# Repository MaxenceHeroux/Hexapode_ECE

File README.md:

# Hexapode ECE

Robot hexapode (6 pattes, 18 servos Dynamixel AX-12A) du FabLab ECE MAKERS,
piloté par une Raspberry Pi 4 sous Ubuntu 22.04 / ROS 2 Humble. Ce dépôt
contient la carte électronique d'alimentation, le code de pilotage des servos,
le modèle et la marche sous ROS 2, et la documentation de mise en route.

Version actuelle : **v1.0.0** — voir [CHANGELOG.md](CHANGELOG.md).

## Ce que sait faire le robot

| | |
|---|---|
| **Marcher** | trépied avec recouvrement des appuis (aussi tétrapode, onde) piloté au clavier ou par Foxglove (`/cmd_vel`) : avancer, reculer, crabe, tourner ; jusqu'à 0,22 m/s et 0,8 rad/s |
| **Régler sa hauteur** | 50 à 150 mm en marchant (`t` / `b`), l'écart des pieds s'adapte tout seul aux butées |
| **Se stabiliser (IMU)** | tient son cap, reste horizontal si le sol penche, ne s'affaisse plus à chaque pas, s'arrête s'il bascule ; la rotation est asservie au gyroscope (compense le patinage) |
| **Faire des figures** | coucou, danse, cabrer, cœur (fenêtre « Actions hexapode ») |
| **Se dépanner** | remise en route des moteurs en une touche (`r`), servos bloqués remis en route automatiquement, reconnexion si la liaison décroche |
| **Marcher sans fil** | la Pi fait son hotspot Wi-Fi au démarrage, servos et IMU démarrent seuls ; le câble reste prioritaire quand il est branché |
| **Se voir** | modèle 3D (maillages SolidWorks) dans RViz et Foxglove |

## Démarrage rapide

Tout se lance depuis le PC (Ubuntu + ROS 2 Humble) avec **une seule commande** :

```bash
cd ~/Hexapode2026/Hexapode_ECE/ros2_ws
./hexapode.sh                   # simulation : marche + Foxglove + clavier (aucun servo ne bouge)
./hexapode.sh dry               # + pont vers le robot SANS envoi (vérifie servos et butées)
./hexapode.sh robot             # le robot se lève puis marche — PC et Pi reliés par CÂBLE
./hexapode.sh robot-distance    # pareil SANS CÂBLE : le PC rejoint le hotspot Wi-Fi de la Pi (voir hotspot.md)
./hexapode.sh dry-distance      # vérification sans câble
```

Le script règle l'environnement ROS (CycloneDDS, liaison câble ou Wi-Fi), arrête une
session oubliée, ouvre **Foxglove** (déjà connecté) et une fenêtre **« Teleop hexapode »**,
puis lance la marche et, selon le mode, le pont vers le robot. `robot-distance` allume en
au hotspot de la Pi (sauf si le câble est branché : il reste prioritaire), attend la Pi et
démarre `leg_server` dessus si besoin.

**Piloter** (clavier AZERTY, dans « Teleop hexapode ») :

| Touche | Effet |
|---|---|
| `i` / `,` | avancer / reculer (maintenir la touche) |
| `j` / `l` | tourner à gauche / à droite |
| Maj + `J` / `L` | crabe gauche / droite |
| `t` / `b` | monter / descendre le corps (doucement) |
| `k` | stop |

**Figures et remise en route** (fenêtre « Actions hexapode ») : `1` coucou, `2` danse,
`3` cabrer, `4` cœur, `0` arrêter ; **`r` remet les moteurs en route** quand ça bloque.

| `q` / `z` | vitesse +10 % / −10 % (max 0,20 m/s) |

**Arrêter** : Ctrl+C dans le terminal du lancement → le robot se fige, couple gardé.
Le relâcher : `nc 192.168.137.10 5555` (ou `10.42.0.10` en Wi-Fi) puis `ESTOP`.
Après `robot-distance`, Ctrl+C **ramène aussi le PC sur un Wi-Fi avec internet** (ou à tout
moment : `./hexapode.sh internet`).

Avant un essai sur le robot : batterie ≥ 11 V, robot posé au sol, quelqu'un à côté de
l'alimentation. Détails : [ros2_ws/src/hexapod_control/docs/lancement.md](ros2_ws/src/hexapod_control/docs/lancement.md).

## Index

| Document | Contenu |
|---|---|
| [setup.md](setup.md) | Mise en route de la Raspberry Pi : connexion SSH (`ssh hexapode`), réseau et partage de connexion par câble, VS Code, mises à jour, sauvegardes, synchronisation git PC ↔ Pi |
| [hotspot.md](hotspot.md) | **Sans câble** : hotspot Wi-Fi de la Pi, le PC s'y connecte (`ssh hexapode-wifi`, `hexapode.sh robot-distance`) ; câble prioritaire ; dépannage |
| [ros2_ws/README.md](ros2_ws/README.md) | Espace de travail ROS 2 : environnement, paquets, lancement, Foxglove |
| [ros2_ws/src/hexapod_imu/README.md](ros2_ws/src/hexapod_imu/README.md) | IMU : nœud `/imu/data` sur la Pi, calibration, dépannage |
| [PCB/Neuro_IMU/branchement.md](PCB/Neuro_IMU/branchement.md) | Carte IMU maison (LSM6DSV16X) : branchement I2C sur la Pi, brochage de la Pi 4 |
| [ros2_ws/src/hexapod_control/docs/](ros2_ws/src/hexapod_control/docs) | Nœuds ROS : [lancement](ros2_ws/src/hexapod_control/docs/lancement.md), [marche `gait_node`](ros2_ws/src/hexapod_control/docs/gait_node.md), [pont `leg_server_bridge`](ros2_ws/src/hexapod_control/docs/leg_server_bridge.md) |
| [Dyna_test/dyna.md](Dyna_test/dyna.md) | Servos Dynamixel : `leg_server` (Pi) et son protocole, interface graphique des 6 pattes et cinématique (PC), réglages des servos, port `/dev/u2d2` |
| [Dyna_test/test_torque.md](Dyna_test/test_torque.md) | `test_torque` : lever le robot (`--home` étoile de mer), options, essais |
| [Dyna_test/Torque_calcul.md](Dyna_test/Torque_calcul.md) | Calcul du couple demandé aux servos, essais du 25/11/2026, résultats et graphiques |
| [tps_archi.md](tps_archi.md) | Plan d'action ROS 2 : URDF, ros2_control, interface web, réseau ROS, capteurs, simulation et apprentissage par renforcement |
| [graphify-out/GRAPH_REPORT.md](graphify-out/GRAPH_REPORT.md) | Graphe de connaissances du dépôt (`graph.html` à ouvrir dans un navigateur) |

## Dossiers

| Dossier | Contenu |
|---|---|
| [`ros2_ws/`](ros2_ws) | ROS 2 : `hexapode.sh` (lancement), `hexapode_env.sh` (environnement), `hexapod_description` (URDF, maillages SolidWorks), `hexapod_control` (marche, pont vers le robot), `hexapod_bringup` (CycloneDDS) |
| [`Dyna_test/`](Dyna_test) | code Dynamixel : `src/leg_server.cpp`, `gui/` (interface, modèle, `test_torque`, calibration `leg_gui_config.json`, mesures), règle udev, réglages, docs, `graphs/` |
| [`PCB/`](PCB) | carte d'alimentation / Dynamixel (KiCad, Gerbers, fichiers JLCPCB) |
| [`graphify-out/`](graphify-out) | graphe de connaissances du dépôt (graphify) |

## Sans ROS (outils de calibration et d'essai)

```bash
ssh hexapode "cd ~/Hexapode_ECE/Dyna_test && (nohup ./bin/leg_server > /tmp/leg_server.log 2>&1 &)"   # sur la Pi
python3 Dyna_test/gui/leg_gui.py                    # interface des pattes, sur le PC
python3 Dyna_test/gui/test_torque.py --home         # lever / reposer le robot
```

Ne pas les utiliser en même temps que `hexapode.sh robot` (un seul programme doit
commander les servos).

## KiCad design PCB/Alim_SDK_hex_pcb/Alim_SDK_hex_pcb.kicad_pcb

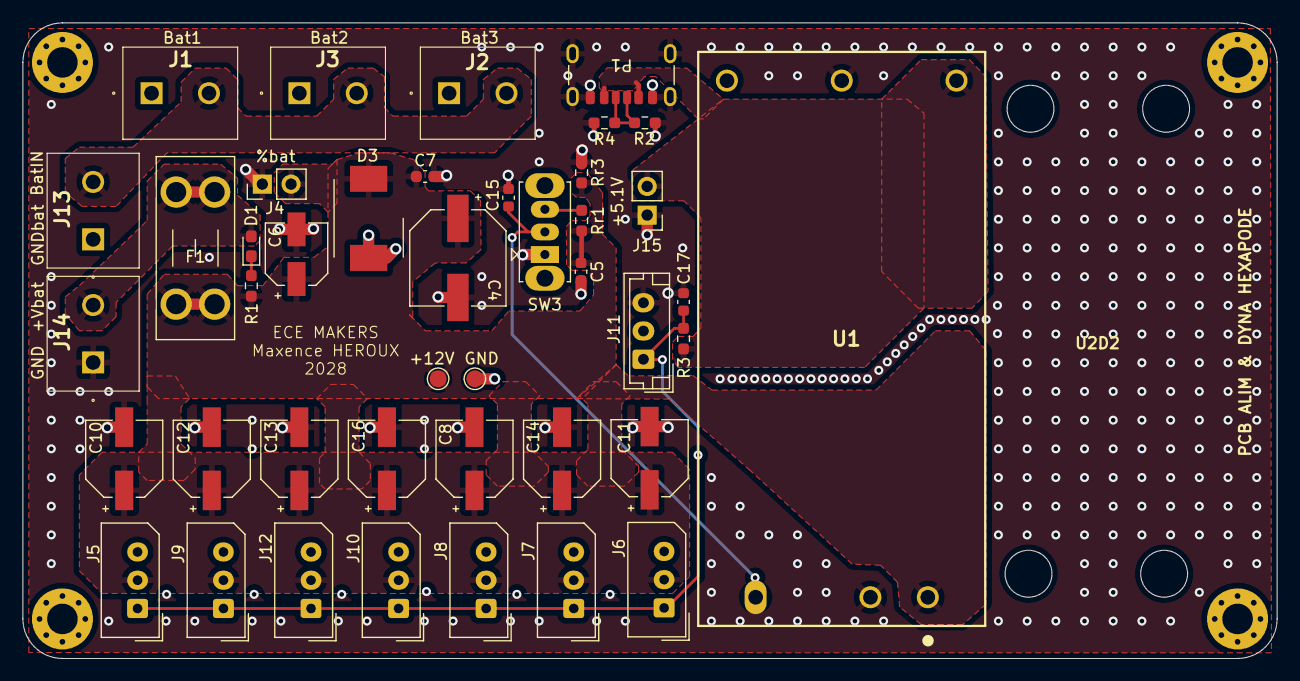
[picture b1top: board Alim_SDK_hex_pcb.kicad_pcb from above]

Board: 2 copper layers, 111.0 x 56.3 mm, 42 parts (0 on the bottom side), 11 nets.

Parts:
+12V: TestPoint_Pad_D1.5mm
C4: 220uF 35v; CP_Wurth_WCAP-HSG5-D8L10.5
C5: 10 μF / 25 V1812 MLCC; C_0603_1608Metric
C6: 10uF 50v; CP_Wurth_WCAP-HSG5-D5L5.8
C7: 100nF 50v; C_0603_1608Metric
C8, C10, C11, C12, C13, C14, C16: 100 uF 35v; CP_Wurth_WCAP-HSG5-D6.3L5.8
C15: 100nF 25v; C_0603_1608Metric
C17: 10 nF; C_0603_1608Metric
D1: LED; LED_0603_1608Metric_Pad1.05x0.95mm_HandSolder
D3: 824540241; D_Wurth_WE-TVSP-DO214-AB-1500W_UNI
F1: Fuse; Fuseholder_Blade_Mini_Keystone_3568
GND: TestPoint_Pad_D1.5mm
J1, J2, J3, J13, J14: 1729128
J4, J15: conn_GPIO; PinHeader_1x02_P2.54mm_Vertical
J5, J6, J7, J8, J9, J10, J12: 22-03-5035; Molex_SPOX_5267-03A_1x03_P2.50mm_Vertical_maxou2
J11: B3B-EH-A_LF__SN_; JST_EH_B3B-EH-A_1x03_P2.50mm_Vertical
P1: USB_C_Plug_USB2.0; USB_C_Receptacle_GCT_USB4125-xx-x_6P_TopMnt_Horizontal
R1: 500; R_0603_1608Metric_Pad0.98x0.95mm_HandSolder
R2: 5K1; R_0603_1608Metric_Pad0.98x0.95mm_HandSolder
R3: 10k; R_0603_1608Metric_Pad0.98x0.95mm_HandSolder
R4: 5k1; R_0603_1608Metric_Pad0.98x0.95mm_HandSolder
Rr1, Rr3: 1k; R_0603_1608Metric_Pad0.98x0.95mm_HandSolder
SW3: SW_Nidec_CAS-120A1; SW_Slide_SPDT_Straight_CK_OS102011MS2Q
U1: TEN_30-1211; TEN-30-1211

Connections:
+5.1V: J15.2, P1.A9 (VBUS), P1.B9 (VBUS), R3.1, U1.4 (+VOUT)
+12V: +12V.1, C4.1, C5.1, C6.1, C7.1, C8.1, C10.1, C11.1, C12.1, C13.1, C14.1, C16.1, D3.1 (K), F1.2, J4.2, J5.2, J6.2, J7.2, J8.2, J9.2, J10.2, J12.2, R1.2, Rr1.2, Rr3.2, U1.1 (+VIN_(VCC))
+VBatIn: J1.2, J2.2, J3.2, J13.2
+Vbat: D1.2 (A), F1.1, J14.2
/Dynamixel_hex_pcb/Data_dyna: C17.1, J5.1, J6.1, J7.1, J8.1, J9.1, J10.1, J11.1, J12.1, R3.2
/EN_traco12: C15.1, SW3.2 (B), U1.3 (REMOTE_ON/OFF)
GND: C4.2, C5.2, C6.2, C7.2, C8.2, C10.2, C11.2, C12.2, C13.2, C14.2, C15.2, C16.2, C17.2, D3.2 (A), GND.1, J4.1, J5.3, J6.3, J7.3, J8.3, J9.3, J10.3, J11.3, J12.3, J14.1, J15.1, P1.A12 (GND), P1.B12 (GND), P1.S1 (SHIELD), R2.2, R4.2, Rr3.1, SW3.1 (C), U1.2 (-VIN_(GND)), U1.5 (-VOUT)
GND_BAT: J1.1, J2.1, J3.1, J13.1
unnamed: D1.1 (K), R1.1
unnamed: P1.A5 (CC), P1.B5 (VCONN), R2.1, R4.1
unnamed: Rr1.1, SW3.3 (A)
